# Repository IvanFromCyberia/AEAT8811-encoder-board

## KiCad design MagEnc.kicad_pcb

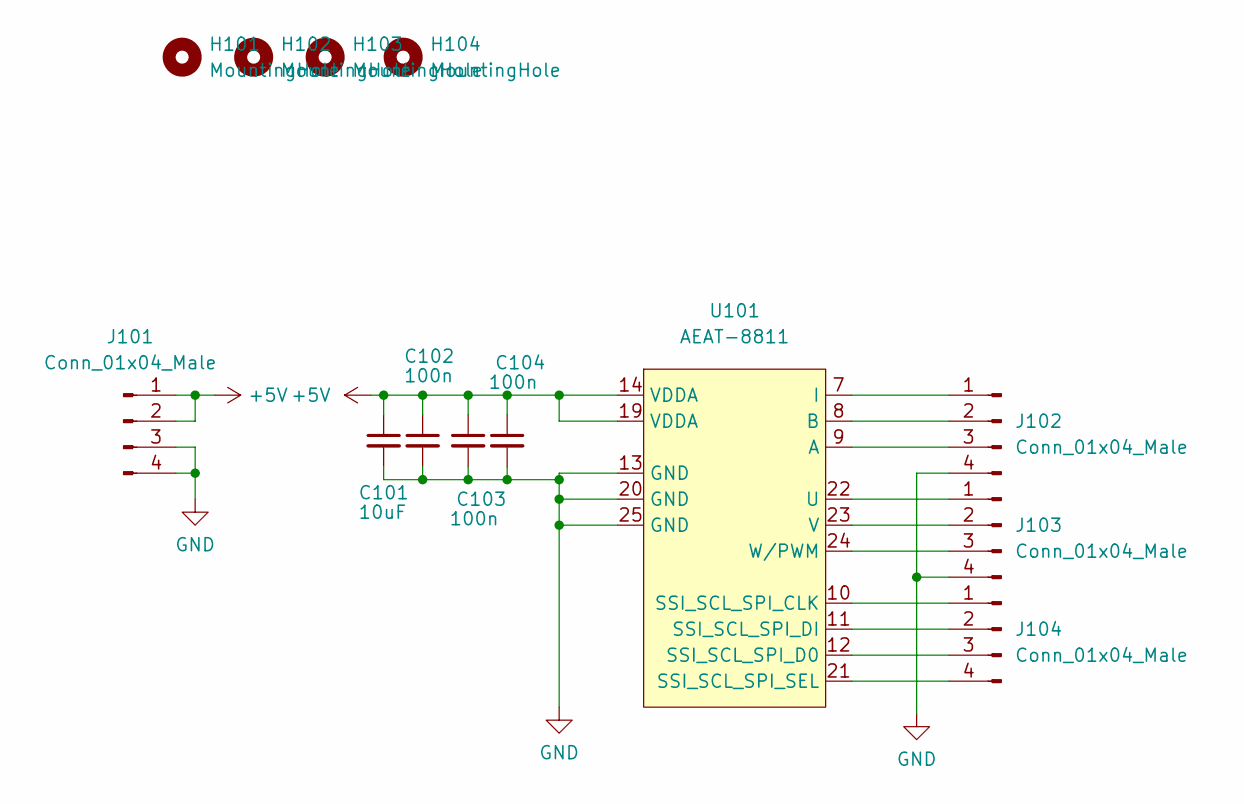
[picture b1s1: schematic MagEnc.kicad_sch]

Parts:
C101: 10uF; C_1210_3225Metric
C102: 100n; C_0805_2012Metric
C103, C104: 100n; C_0603_1608Metric
H101, H102, H103, H104: MountingHole; MountingHole_2.5mm
J101, J102, J103, J104: Conn_01x04_Male; PinHeader_1x04_P2.54mm_Vertical
U101: AEAT-8811; QFN-24-1EP_5x5mm_P0.65mm_EP3.4x3.4mm

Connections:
+5V: C101.1, C102.1, C103.1, C104.1, J101.1, J101.2, U101.14 (VDDA), U101.19 (VDDA)
GND: C101.2, C102.2, C103.2, C104.2, J101.3, J101.4, J102.4, J103.4, U101.13 (GND), U101.20 (GND), U101.25 (GND)
unnamed: J102.1, U101.7 (I)
unnamed: J102.2, U101.8 (B)
unnamed: J102.3, U101.9 (A)
unnamed: J103.1, U101.22 (U)
unnamed: J103.2, U101.23 (V)
unnamed: J103.3, U101.24 (W/PWM)
unnamed: J104.1, U101.10 (SSI_SCL_SPI_CLK)
unnamed: J104.2, U101.11 (SSI_SCL_SPI_DI)
unnamed: J104.3, U101.12 (SSI_SCL_SPI_D0)
unnamed: J104.4, U101.21 (SSI_SCL_SPI_SEL)

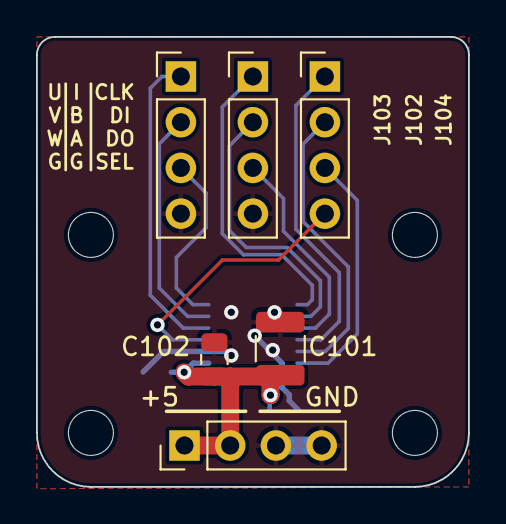
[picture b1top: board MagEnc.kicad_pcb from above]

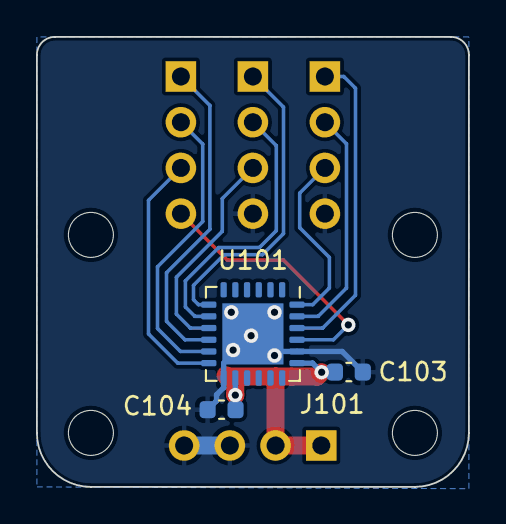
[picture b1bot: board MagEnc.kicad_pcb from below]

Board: 2 copper layers, 24.0 x 25.0 mm, 13 parts (3 on the bottom side), 12 nets.

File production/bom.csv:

Designator,Footprint,Quantity,Value,LCSC Part #
C101,C_1210_3225Metric,1,10uF,
C102,C_0805_2012Metric,1,100n,
"C103, C104",C_0603_1608Metric,2,100n,
"H101, H102, H103, H104",MountingHole_2.5mm,4,MountingHole,
"J101, J102, J103, J104",PinHeader_1x04_P2.54mm_Vertical,4,Conn_01x04_Male,
U101,QFN-24-1EP_5x5mm_P0.65mm_EP3.4x3.4mm,1,AEAT-8811,

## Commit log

2022-10-23 Update for production
    Undate for production
